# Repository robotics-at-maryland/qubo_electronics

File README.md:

# qubo_electronics

Welcome to the electronics repo for Project QUBO.
QUBO is an autonomous underwater vehicle and all of its electronics designs are stored here.

We use EAGLE for our circuit CAD.

eagleLibraries stores all the eagle libraries.

eagleDesigns sores all the boards that we design. Any design in this folder should ONLY USE COMPONENTS FROM THE eagleLibraries FOLDER.

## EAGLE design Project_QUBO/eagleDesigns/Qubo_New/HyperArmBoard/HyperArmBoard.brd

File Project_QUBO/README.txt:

This is the electronics folder for Project QUBO, the replacement for Tortuga 4.
===============================================================================

eagleLibraries is the EAGLE library folder.
	ALL robot PCB designs MUST only contain parts from libraries in the eagleLibraries directory.

datasheets is for all part datasheets used in the electronics designs.
	No subdirectories

eagleDesigns is for the actual eagle design files. 
	Subdirectories are created on a BOARD-BY-BOARD basis.
	If you're creating a new PCB, make a new folder. If you're editing an existing board, stay in the same folder.
	Use reason when creating new versions of files.

designDocumentation  is for design documentation.
	Use reason with file naming, no subdirectories.
	Document your design process ie. what your goal is, what options you considered, why you chose what you did, outline your final design selection, etc.
	Brownie points for LaTeX

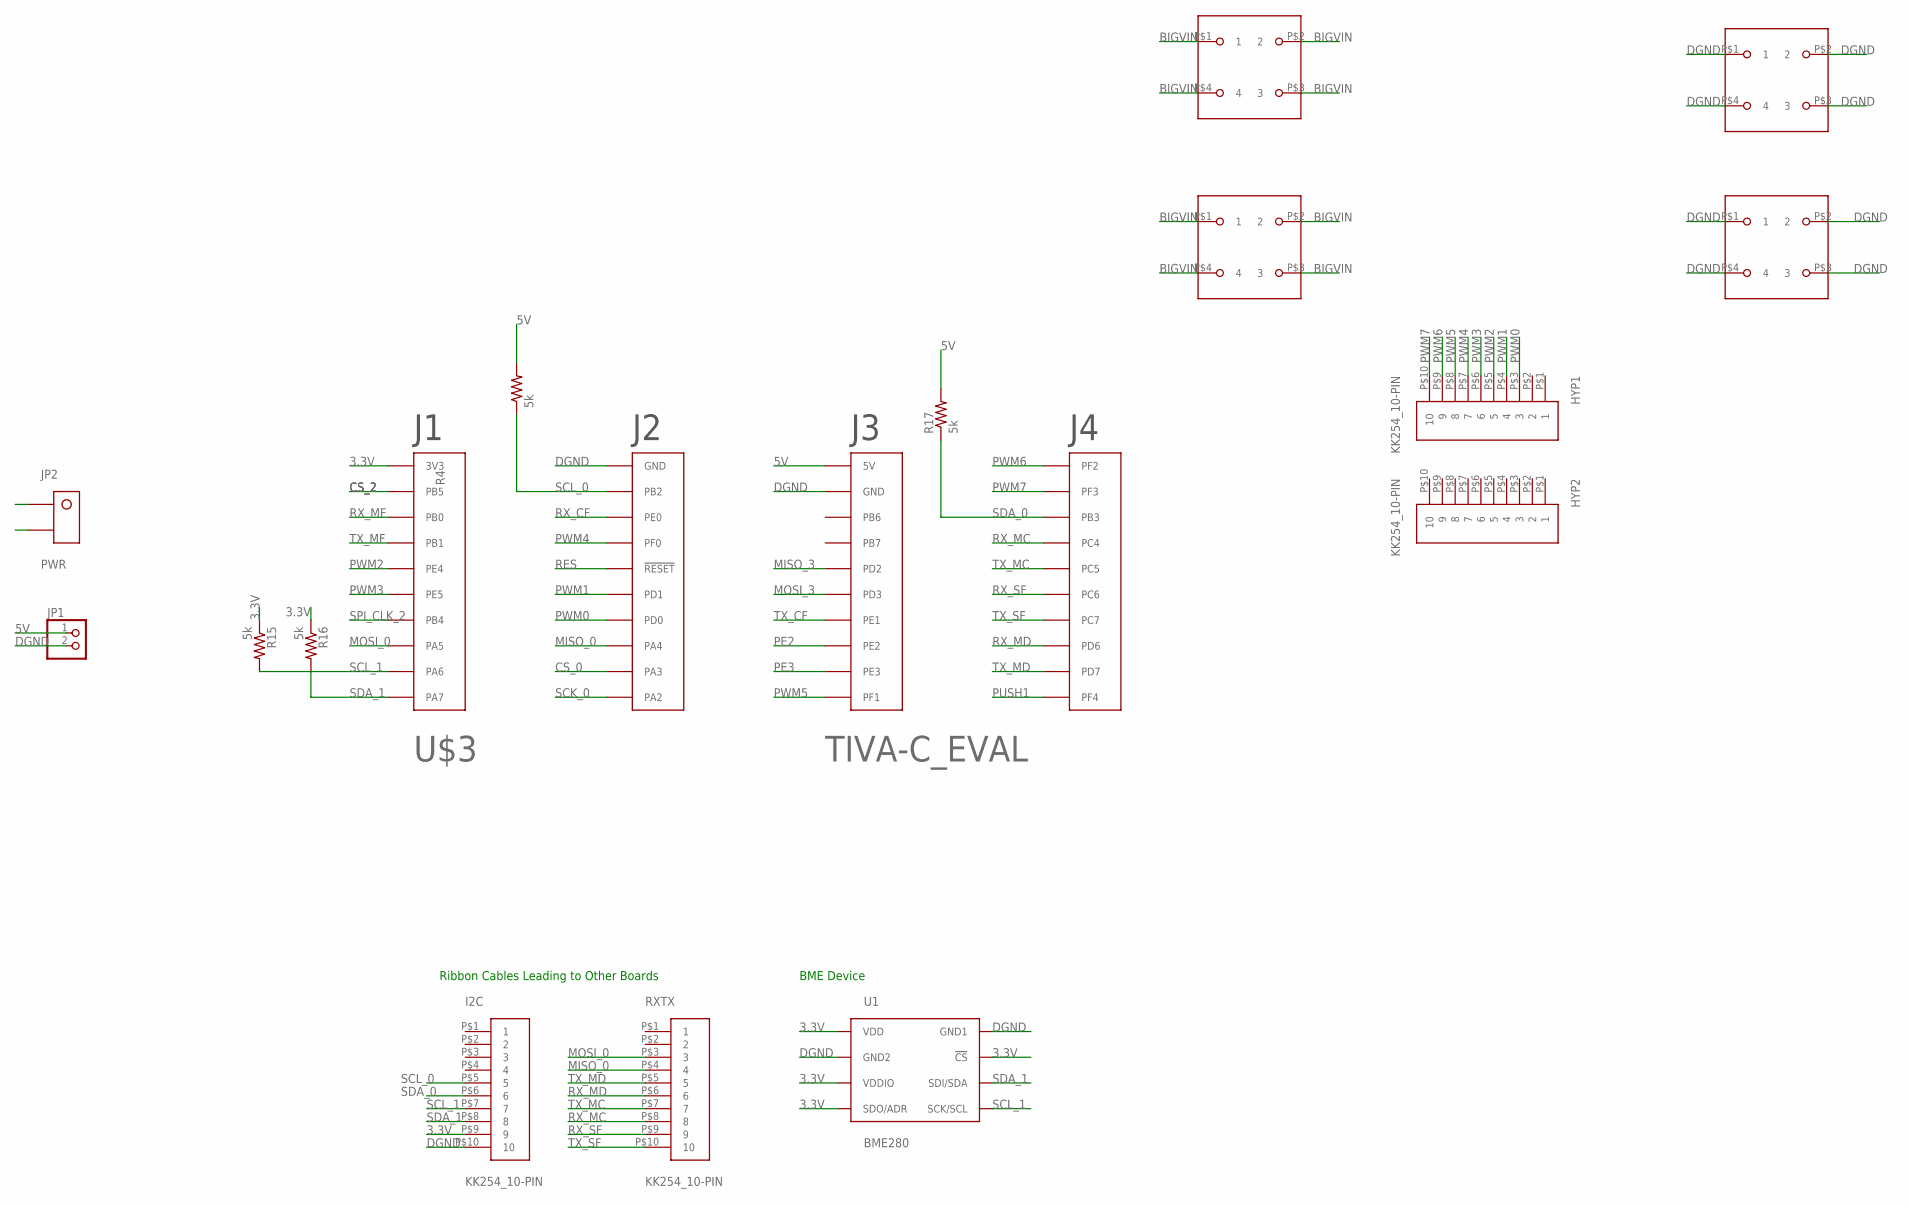
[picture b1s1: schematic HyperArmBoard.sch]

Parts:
HYP1, HYP2: KK254_10-PIN
I2C: KK254_10-PIN
JP1: PINHD-1X2; 1X02
JP2: PWR; SUPERSABRE_2CIRCUIT
R4, R15, R16, R17: 5k; R0805
RXTX: KK254_10-PIN
U1: BME280; BME280_LGA
U$3: TIVA-C_EVAL
U$4, U$5, U$6, U$7: BCS-106-L-D-PE-BE; 4-PIN-BIGPOWER

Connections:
3.3V: I2C.P$9 (9), R15.1, R16.1, U1.P$2 (!CS), U1.P$5 (SDO/ADR), U1.P$6 (VDDIO), U1.P$8 (VDD), U$3.1-1 (3V3)
5V: JP1.1, R4.2, R17.2, U$3.3-1 (5V)
BIGVIN: JP2.P$1, U$4.P$1 (1), U$4.P$2 (2), U$4.P$3 (3), U$4.P$4 (4), U$5.P$1 (1), U$5.P$2 (2), U$5.P$3 (3), U$5.P$4 (4)
CS_0: U$3.2-9 (PA3)
CS_2: U$3.1-2 (PB5)
DGND: I2C.P$10 (10), JP1.2, JP2.P$2, U1.P$1 (GND1), U1.P$7 (GND2), U$3.2-1 (GND), U$3.3-2 (GND), U$6.P$1 (1), U$6.P$2 (2), U$6.P$3 (3), U$6.P$4 (4), U$7.P$1 (1), U$7.P$2 (2), U$7.P$3 (3), U$7.P$4 (4)
MISO_0: RXTX.P$4 (4), U$3.2-8 (PA4)
MISO_3: U$3.3-5 (PD2)
MOSI_0: RXTX.P$3 (3), U$3.1-8 (PA5)
MOSI_3: U$3.3-6 (PD3)
PE2: U$3.3-8 (PE2)
PE3: U$3.3-9 (PE3)
PUSH1: U$3.4-10 (PF4)
PWM0: HYP1.P$3 (3), U$3.2-7 (PD0)
PWM1: HYP1.P$4 (4), U$3.2-6 (PD1)
PWM2: HYP1.P$5 (5), U$3.1-5 (PE4)
PWM3: HYP1.P$6 (6), U$3.1-6 (PE5)
PWM4: HYP1.P$7 (7), U$3.2-4 (PF0)
PWM5: HYP1.P$8 (8), U$3.3-10 (PF1)
PWM6: HYP1.P$9 (9), U$3.4-1 (PF2)
PWM7: HYP1.P$10 (10), U$3.4-2 (PF3)
RES: U$3.2-5 (!RESET!)
RX_CF: U$3.2-3 (PE0)
RX_MC: RXTX.P$8 (8), U$3.4-4 (PC4)
RX_MD: RXTX.P$6 (6), U$3.4-8 (PD6)
RX_MF: U$3.1-3 (PB0)
RX_SF: RXTX.P$9 (9), U$3.4-6 (PC6)
SCK_0: U$3.2-10 (PA2)
SCL_0: I2C.P$5 (5), R4.1, U$3.2-2 (PB2)
SCL_1: I2C.P$7 (7), R15.2, U1.P$4 (SCK/SCL), U$3.1-9 (PA6)
SDA_0: I2C.P$6 (6), R17.1, U$3.4-3 (PB3)
SDA_1: I2C.P$8 (8), R16.2, U1.P$3 (SDI/SDA), U$3.1-10 (PA7)
SPI_CLK_2: U$3.1-7 (PB4)
TX_CF: U$3.3-7 (PE1)
TX_MC: RXTX.P$7 (7), U$3.4-5 (PC5)
TX_MD: RXTX.P$5 (5), U$3.4-9 (PD7)
TX_MF: U$3.1-4 (PB1)
TX_SF: RXTX.P$10 (10), U$3.4-7 (PC7)

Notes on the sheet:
Ribbon Cables Leading to Other Boards
BME Device

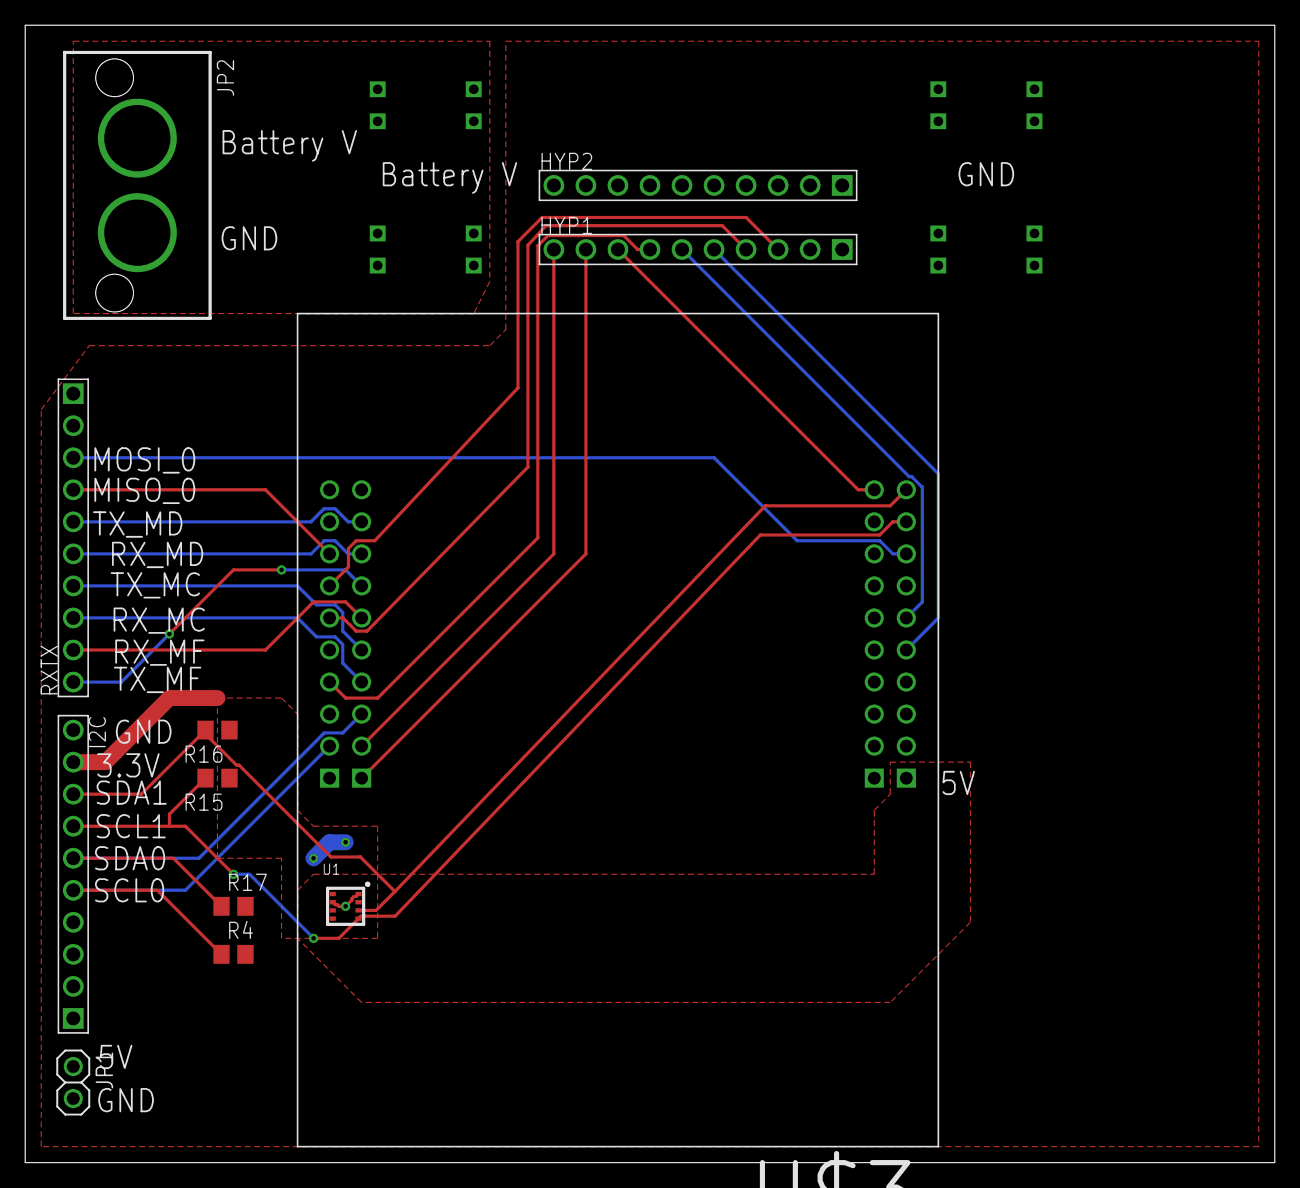
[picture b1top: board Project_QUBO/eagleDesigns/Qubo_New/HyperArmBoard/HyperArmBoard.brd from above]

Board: 2 copper layers, 99.1 x 90.2 mm, 16 parts (0 on the bottom side), 24 nets.

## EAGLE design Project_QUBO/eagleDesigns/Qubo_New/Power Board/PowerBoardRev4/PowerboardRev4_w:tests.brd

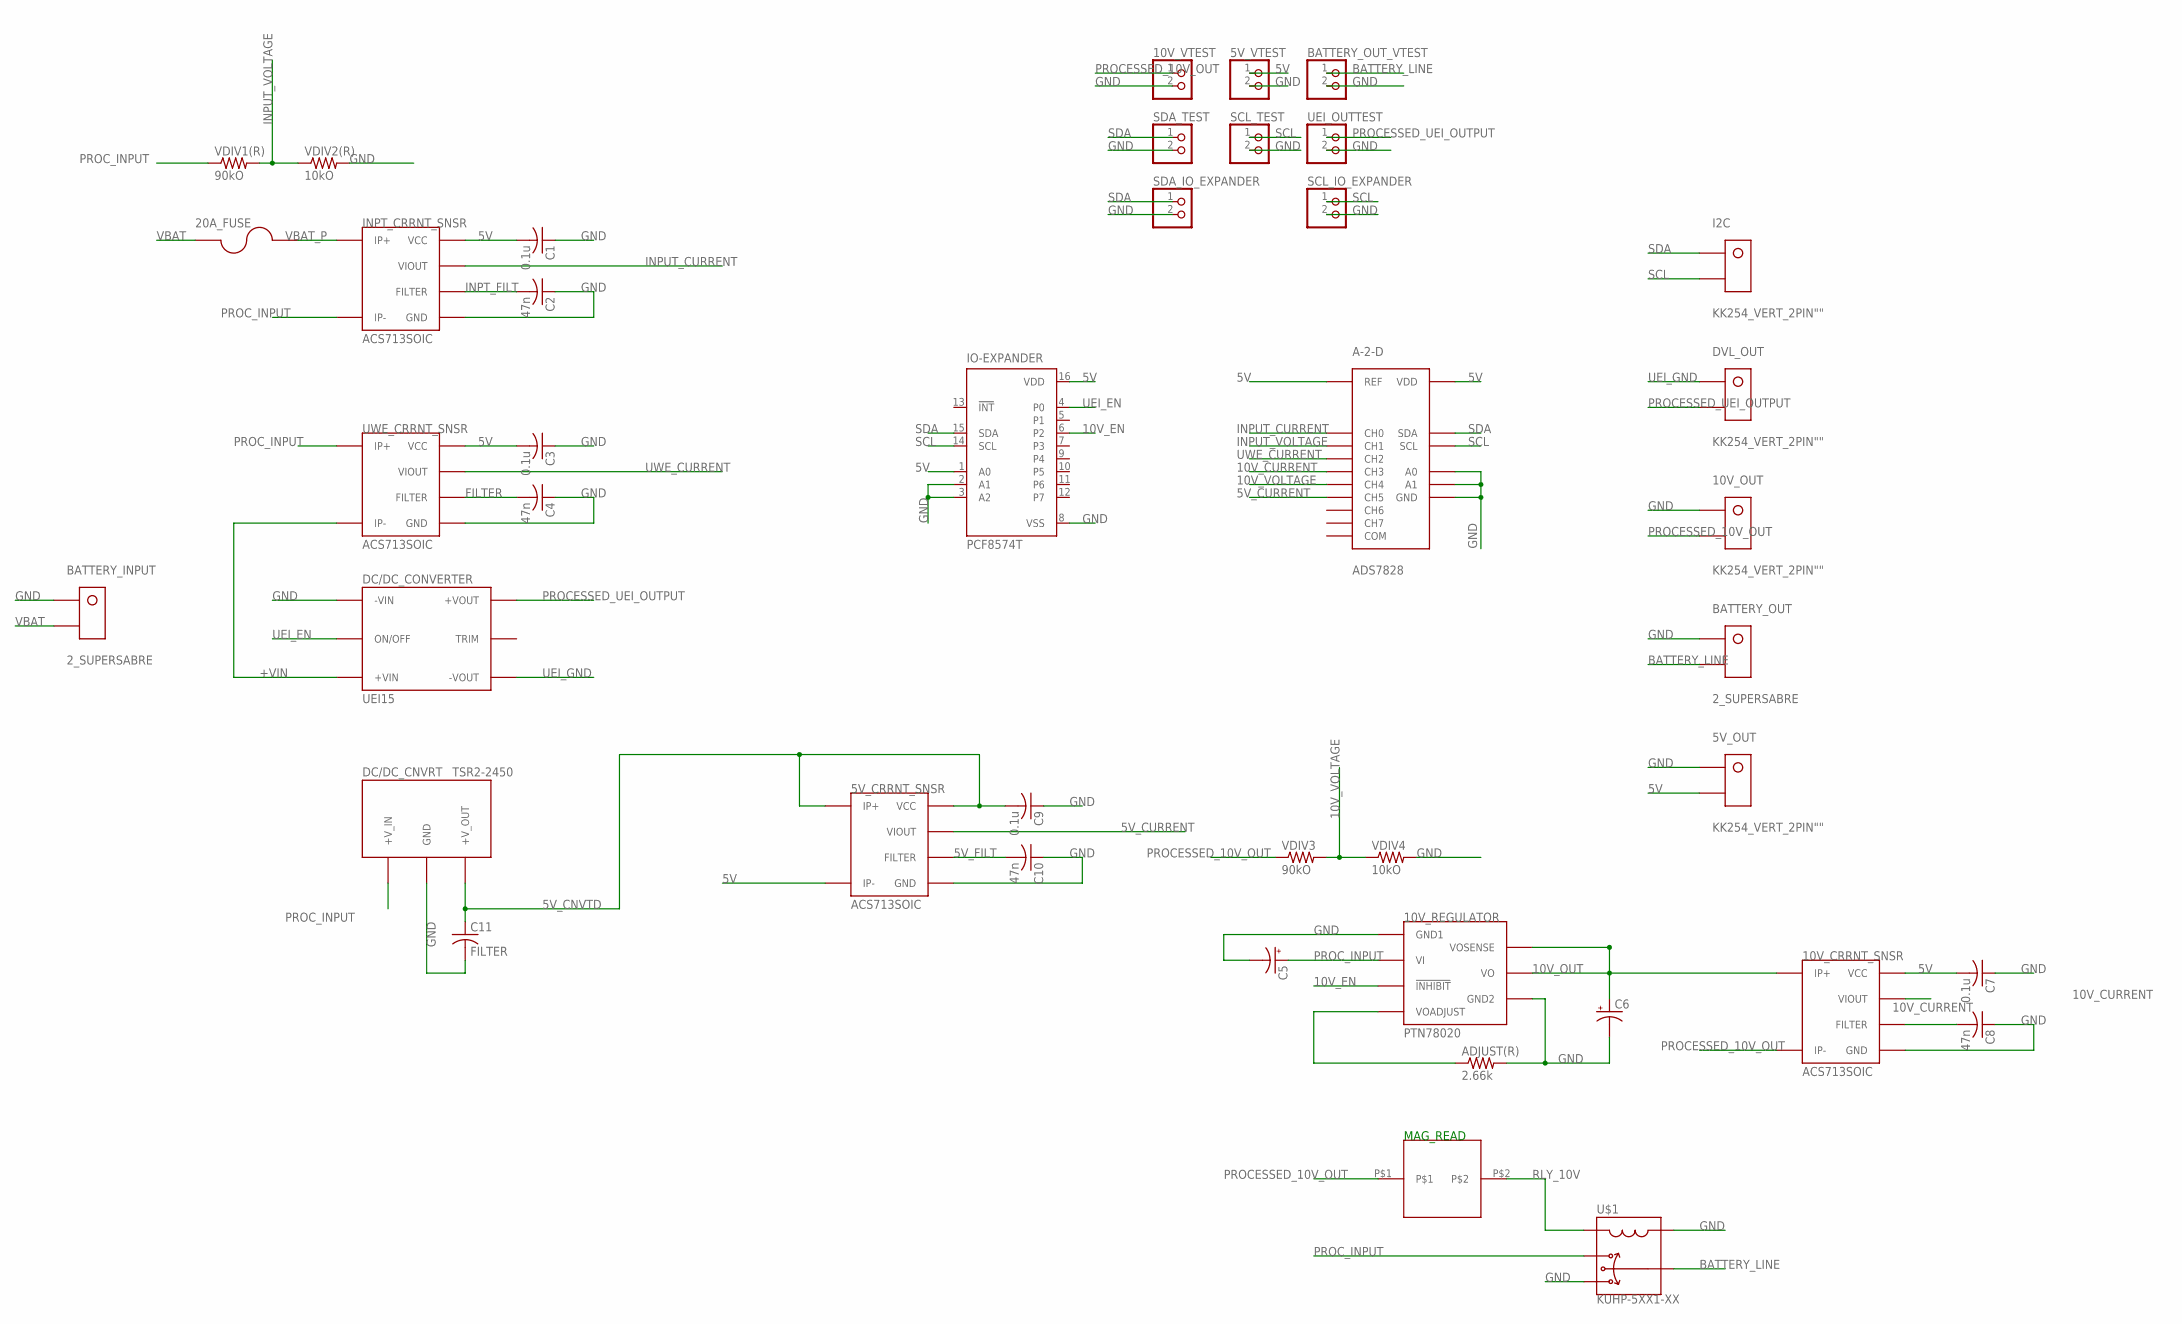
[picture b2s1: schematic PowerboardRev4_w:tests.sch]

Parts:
5V_CRRNT_SNSR, 10V_CRRNT_SNSR: ACS713SOIC; ACS713-SOIC
5V_OUT, 10V_OUT: KK254_VERT_2PIN""; KK254_VERT_2PIN
5V_VTEST, 10V_VTEST: PINHD-1X2; 1X02
10V_REGULATOR: PTN78020; PTN
20A_FUSE: BOWED-1.25"-FUSECLIPS; 1.25"_FUSECLIPS
A-2-D: ADS7828; TSSOP16
ADJUST(R): 2.66k; R0805
BATTERY_INPUT: 2_SUPERSABRE; SUPERSABRE_2CIRCUIT
BATTERY_OUT: 2_SUPERSABRE; SUPERSABRE_2CIRCUIT
BATTERY_OUT_VTEST: PINHD-1X2; 1X02
C1, C3, C7, C9: 0.1u; C0805
C2, C4, C8, C10: 47n; C0805
C5, C6: CPOL-US; PANASONIC_A_TYPE_M
C11: FILTER; C0805
DC/DC_CNVRT: TSR2-2450; TSR2
DC/DC_CONVERTER: UEI15
DVL_OUT: KK254_VERT_2PIN""; KK254_VERT_2PIN
I2C: KK254_VERT_2PIN""; KK254_VERT_2PIN
INPT_CRRNT_SNSR: ACS713SOIC; ACS713-SOIC
IO-EXPANDER: PCF8574T; SO16W
MAGREAD: HE151TR-ND
SCL_IO_EXPANDER: PINHD-1X2; 1X02
SCL_TEST: PINHD-1X2; 1X02
SDA_IO_EXPANDER: PINHD-1X2; 1X02
SDA_TEST: PINHD-1X2; 1X02
U$1: KUHP-5XX1-XX; KUHP_6.35MM-QUICK-CONNECT
UEI_OUTTEST: PINHD-1X2; 1X02
UWE_CRRNT_SNSR: ACS713SOIC; ACS713-SOIC
VDIV1(R), VDIV3: 90kO; R0805
VDIV2(R), VDIV4: 10kO; R0805

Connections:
5V: 5V_CRRNT_SNSR.P$3 (IP-), 5V_CRRNT_SNSR.P$4 (IP-), 5V_OUT.P$2, 5V_VTEST.1, 10V_CRRNT_SNSR.P$8 (VCC), A-2-D.10 (REF), A-2-D.16 (VDD), C1.2, C3.2, C7.2, INPT_CRRNT_SNSR.P$8 (VCC), IO-EXPANDER.1 (A0), IO-EXPANDER.16 (VDD), UWE_CRRNT_SNSR.P$8 (VCC)
5V_CNVTD: 5V_CRRNT_SNSR.P$1 (IP+), 5V_CRRNT_SNSR.P$2 (IP+), 5V_CRRNT_SNSR.P$8 (VCC), C9.2, C11.1, DC/DC_CNVRT.3 (+V_OUT)
5V_CURRENT: 5V_CRRNT_SNSR.P$7 (VIOUT), A-2-D.6 (CH5)
5V_FILT: 5V_CRRNT_SNSR.P$6 (FILTER), C10.2
10V_CURRENT: 10V_CRRNT_SNSR.P$7 (VIOUT), A-2-D.4 (CH3)
10V_EN: 10V_REGULATOR.INHIBIT (!INHIBIT!), IO-EXPANDER.6 (P2)
10V_OUT: 10V_CRRNT_SNSR.P$1 (IP+), 10V_CRRNT_SNSR.P$2 (IP+), 10V_REGULATOR.SENSE (VOSENSE), 10V_REGULATOR.VOUT (VO), C6.+
10V_VOLTAGE: A-2-D.5 (CH4), VDIV3.2, VDIV4.1
+VIN: DC/DC_CONVERTER.+VIN, UWE_CRRNT_SNSR.P$3 (IP-), UWE_CRRNT_SNSR.P$4 (IP-)
BATTERY_LINE: BATTERY_OUT.P$2, BATTERY_OUT_VTEST.1, U$1.7A (7), U$1.7B (7)
FILTER: C4.2, UWE_CRRNT_SNSR.P$6 (FILTER)
FLTR_10V: 10V_CRRNT_SNSR.P$6 (FILTER), C8.2
GND: 5V_CRRNT_SNSR.P$5 (GND), 5V_OUT.P$1, 5V_VTEST.2, 10V_CRRNT_SNSR.P$5 (GND), 10V_OUT.P$1, 10V_REGULATOR.GND1, 10V_REGULATOR.GND2, 10V_VTEST.2, A-2-D.9 (GND), A-2-D.12 (A0), A-2-D.13 (A1), ADJUST(R).2, BATTERY_INPUT.P$1, BATTERY_OUT.P$1, BATTERY_OUT_VTEST.2, C1.1, C2.1, C3.1, C4.1, C5.-, C6.-, C7.1, C8.1, C9.1, C10.1, C11.2, DC/DC_CNVRT.2 (GND), DC/DC_CONVERTER.-VIN, INPT_CRRNT_SNSR.P$5 (GND), IO-EXPANDER.2 (A1), IO-EXPANDER.3 (A2), IO-EXPANDER.8 (VSS), SCL_IO_EXPANDER.2, SCL_TEST.2, SDA_IO_EXPANDER.2, SDA_TEST.2, U$1.5A (5), U$1.5B (5), U$1.AA (A), U$1.AB (A), UEI_OUTTEST.2, UWE_CRRNT_SNSR.P$5 (GND), VDIV2(R).2, VDIV4.2
INPT_FILT: C2.2, INPT_CRRNT_SNSR.P$6 (FILTER)
INPUT_CURRENT: A-2-D.1 (CH0), INPT_CRRNT_SNSR.P$7 (VIOUT)
INPUT_VOLTAGE: A-2-D.2 (CH1), VDIV1(R).2, VDIV2(R).1
unnamed: 10V_REGULATOR.ADJUST (VOADJUST), ADJUST(R).1
PROCESSED_10V_OUT: 10V_CRRNT_SNSR.P$3 (IP-), 10V_CRRNT_SNSR.P$4 (IP-), 10V_OUT.P$2, 10V_VTEST.1, MAGREAD.P$1, VDIV3.1
PROCESSED_UEI_OUTPUT: DC/DC_CONVERTER.+VOUT, DVL_OUT.P$2, UEI_OUTTEST.1
PROC_INPUT: 10V_REGULATOR.VIN (VI), C5.+, DC/DC_CNVRT.1 (+V_IN), INPT_CRRNT_SNSR.P$3 (IP-), INPT_CRRNT_SNSR.P$4 (IP-), U$1.2A (2), U$1.2B (2), UWE_CRRNT_SNSR.P$1 (IP+), UWE_CRRNT_SNSR.P$2 (IP+), VDIV1(R).1
RLY_10V: MAGREAD.P$2, U$1.BA (B), U$1.BB (B)
SCL: A-2-D.14 (SCL), I2C.P$2, IO-EXPANDER.14 (SCL), SCL_IO_EXPANDER.1, SCL_TEST.1
SDA: A-2-D.15 (SDA), I2C.P$1, IO-EXPANDER.15 (SDA), SDA_IO_EXPANDER.1, SDA_TEST.1
UEI_EN: DC/DC_CONVERTER.ON/OFFCNTRL (ON/OFF), IO-EXPANDER.4 (P0)
UEI_GND: DC/DC_CONVERTER.-VOUT, DVL_OUT.P$1
UWE_CURRENT: A-2-D.3 (CH2), UWE_CRRNT_SNSR.P$7 (VIOUT)
VBAT: 20A_FUSE.P$1, 20A_FUSE.P$2, BATTERY_INPUT.P$2
VBAT_P: 20A_FUSE.P$3, 20A_FUSE.P$4, INPT_CRRNT_SNSR.P$1 (IP+), INPT_CRRNT_SNSR.P$2 (IP+)

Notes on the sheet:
MAG_READ

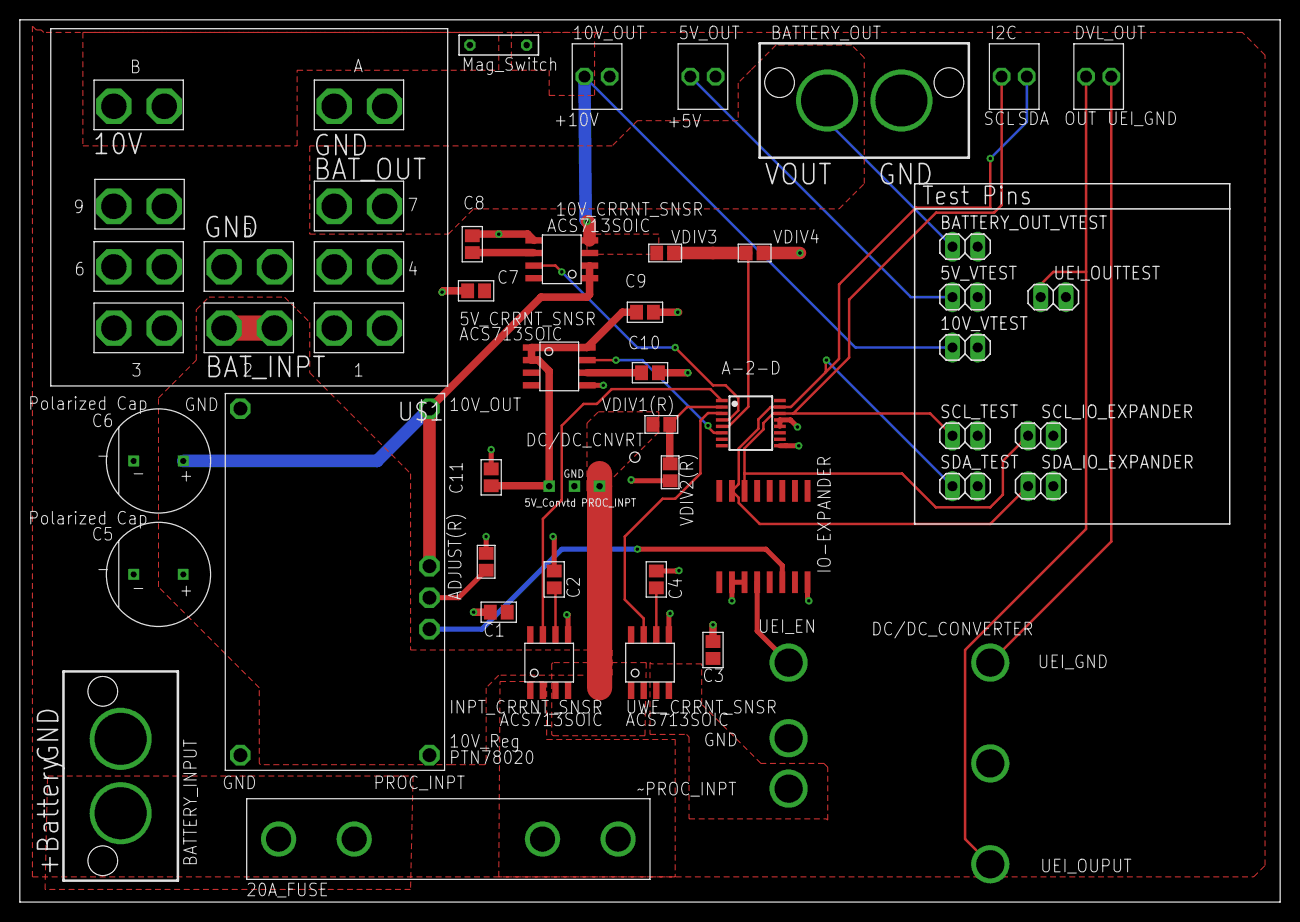
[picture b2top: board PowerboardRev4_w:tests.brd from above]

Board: 2 copper layers, 127.0 x 88.9 mm, 42 parts (0 on the bottom side), 28 nets.

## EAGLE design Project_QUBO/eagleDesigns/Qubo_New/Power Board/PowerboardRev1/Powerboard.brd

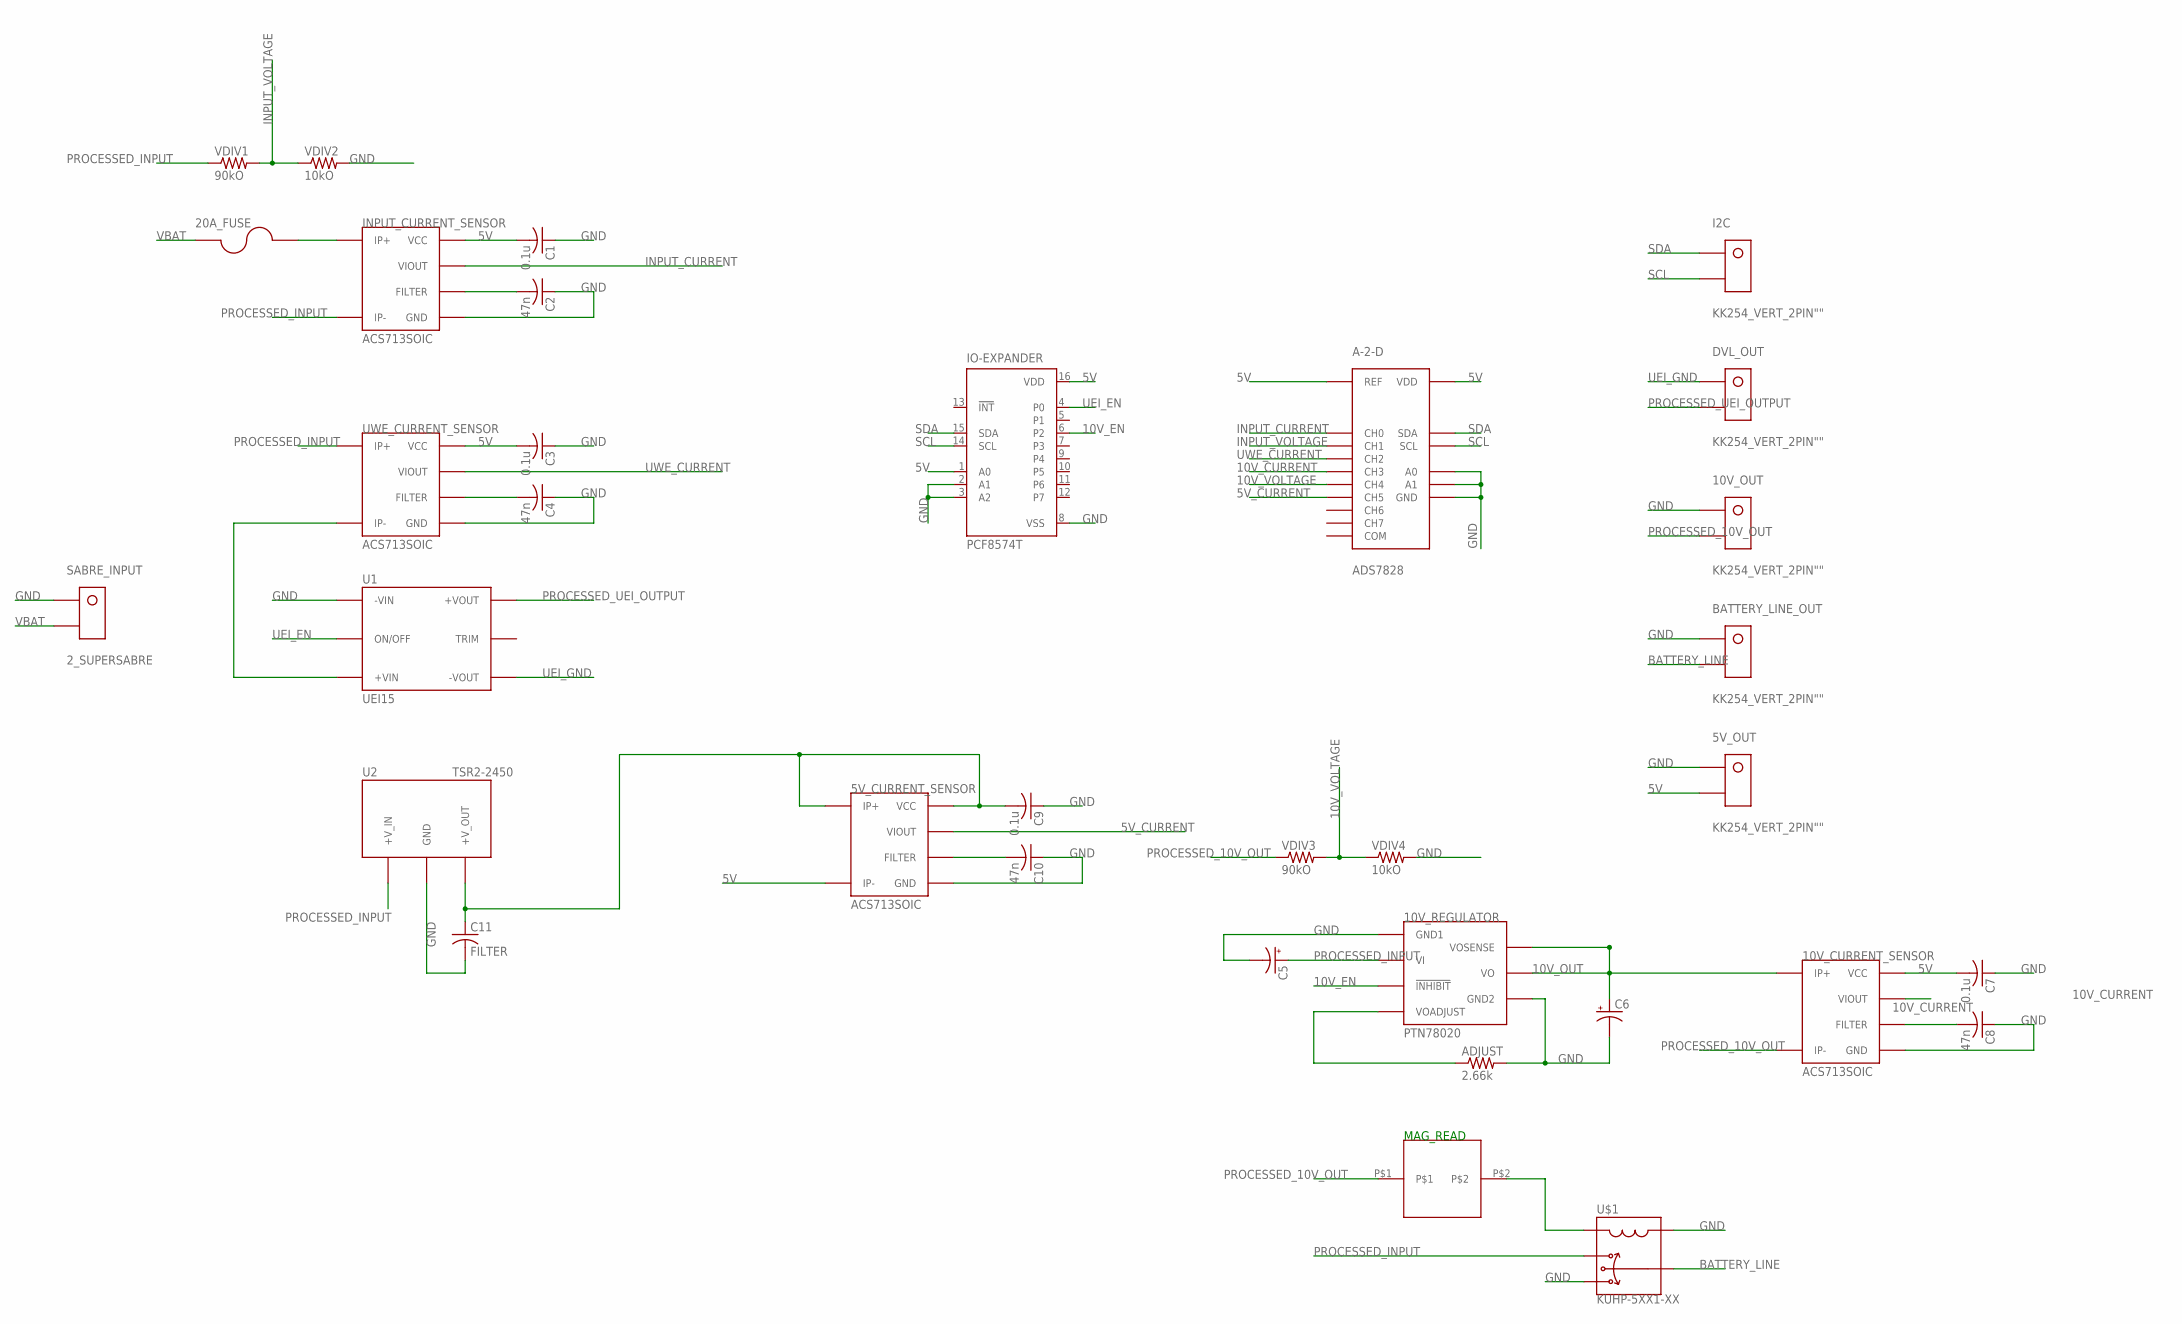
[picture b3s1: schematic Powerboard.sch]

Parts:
5V_CURRENT_SENSOR, 10V_CURRENT_SENSOR: ACS713SOIC; ACS713-SOIC
5V_OUT, 10V_OUT: KK254_VERT_2PIN""; KK254_VERT_2PIN
10V_REGULATOR: PTN78020; PTN
20A_FUSE: BOWED-1.25"-FUSECLIPS; 1.25"_FUSECLIPS
A-2-D: ADS7828; TSSOP16
ADJUST: 2.66k; R0805
BATTERY_LINE_OUT: KK254_VERT_2PIN""; KK254_VERT_2PIN
C1, C3, C7, C9: 0.1u; C0805
C2, C4, C8, C10: 47n; C0805
C5, C6: CPOL-US; PANASONIC_A_TYPE_M
C11: FILTER; C0805
DVL_OUT: KK254_VERT_2PIN""; KK254_VERT_2PIN
I2C: KK254_VERT_2PIN""; KK254_VERT_2PIN
INPUT_CURRENT_SENSOR: ACS713SOIC; ACS713-SOIC
IO-EXPANDER: PCF8574T; SO16W
MAGREAD: HE151TR-ND
SABRE_INPUT: 2_SUPERSABRE; SUPERSABRE_2CIRCUIT
U1: UEI15
U2: TSR2-2450; TSR2
U$1: KUHP-5XX1-XX; KUHP_6.35MM-QUICK-CONNECT
UWE_CURRENT_SENSOR: ACS713SOIC; ACS713-SOIC
VDIV1, VDIV3: 90kO; R0805
VDIV2, VDIV4: 10kO; R0805

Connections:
5V: 5V_CURRENT_SENSOR.P$3 (IP-), 5V_CURRENT_SENSOR.P$4 (IP-), 5V_OUT.P$2, 10V_CURRENT_SENSOR.P$8 (VCC), A-2-D.10 (REF), A-2-D.16 (VDD), C1.2, C3.2, C7.2, INPUT_CURRENT_SENSOR.P$8 (VCC), IO-EXPANDER.1 (A0), IO-EXPANDER.16 (VDD), UWE_CURRENT_SENSOR.P$8 (VCC)
5V_CURRENT: 5V_CURRENT_SENSOR.P$7 (VIOUT), A-2-D.6 (CH5)
10V_CURRENT: 10V_CURRENT_SENSOR.P$7 (VIOUT), A-2-D.4 (CH3)
10V_EN: 10V_REGULATOR.INHIBIT (!INHIBIT!), IO-EXPANDER.6 (P2)
10V_OUT: 10V_CURRENT_SENSOR.P$1 (IP+), 10V_CURRENT_SENSOR.P$2 (IP+), 10V_REGULATOR.SENSE (VOSENSE), 10V_REGULATOR.VOUT (VO), C6.+
10V_VOLTAGE: A-2-D.5 (CH4), VDIV3.2, VDIV4.1
BATTERY_LINE: BATTERY_LINE_OUT.P$2, U$1.7A (7), U$1.7B (7)
GND: 5V_CURRENT_SENSOR.P$5 (GND), 5V_OUT.P$1, 10V_CURRENT_SENSOR.P$5 (GND), 10V_OUT.P$1, 10V_REGULATOR.GND1, 10V_REGULATOR.GND2, A-2-D.9 (GND), A-2-D.12 (A0), A-2-D.13 (A1), ADJUST.2, BATTERY_LINE_OUT.P$1, C1.1, C2.1, C3.1, C4.1, C5.-, C6.-, C7.1, C8.1, C9.1, C10.1, C11.2, INPUT_CURRENT_SENSOR.P$5 (GND), IO-EXPANDER.2 (A1), IO-EXPANDER.3 (A2), IO-EXPANDER.8 (VSS), SABRE_INPUT.P$1, U1.-VIN, U2.2 (GND), U$1.5A (5), U$1.5B (5), U$1.AA (A), U$1.AB (A), UWE_CURRENT_SENSOR.P$5 (GND), VDIV2.2, VDIV4.2
INPUT_CURRENT: A-2-D.1 (CH0), INPUT_CURRENT_SENSOR.P$7 (VIOUT)
INPUT_VOLTAGE: A-2-D.2 (CH1), VDIV1.2, VDIV2.1
unnamed: 20A_FUSE.P$3, 20A_FUSE.P$4, INPUT_CURRENT_SENSOR.P$1 (IP+), INPUT_CURRENT_SENSOR.P$2 (IP+)
unnamed: C2.2, INPUT_CURRENT_SENSOR.P$6 (FILTER)
unnamed: 5V_CURRENT_SENSOR.P$6 (FILTER), C10.2
unnamed: 5V_CURRENT_SENSOR.P$1 (IP+), 5V_CURRENT_SENSOR.P$2 (IP+), 5V_CURRENT_SENSOR.P$8 (VCC), C9.2, C11.1, U2.3 (+V_OUT)
unnamed: 10V_REGULATOR.ADJUST (VOADJUST), ADJUST.1
unnamed: U1.+VIN, UWE_CURRENT_SENSOR.P$3 (IP-), UWE_CURRENT_SENSOR.P$4 (IP-)
unnamed: C4.2, UWE_CURRENT_SENSOR.P$6 (FILTER)
unnamed: MAGREAD.P$2, U$1.BA (B), U$1.BB (B)
unnamed: 10V_CURRENT_SENSOR.P$6 (FILTER), C8.2
PROCESSED_10V_OUT: 10V_CURRENT_SENSOR.P$3 (IP-), 10V_CURRENT_SENSOR.P$4 (IP-), 10V_OUT.P$2, MAGREAD.P$1, VDIV3.1
PROCESSED_INPUT: 10V_REGULATOR.VIN (VI), C5.+, INPUT_CURRENT_SENSOR.P$3 (IP-), INPUT_CURRENT_SENSOR.P$4 (IP-), U2.1 (+V_IN), U$1.2A (2), U$1.2B (2), UWE_CURRENT_SENSOR.P$1 (IP+), UWE_CURRENT_SENSOR.P$2 (IP+), VDIV1.1
PROCESSED_UEI_OUTPUT: DVL_OUT.P$2, U1.+VOUT
SCL: A-2-D.14 (SCL), I2C.P$2, IO-EXPANDER.14 (SCL)
SDA: A-2-D.15 (SDA), I2C.P$1, IO-EXPANDER.15 (SDA)
UEI_EN: IO-EXPANDER.4 (P0), U1.ON/OFFCNTRL (ON/OFF)
UEI_GND: DVL_OUT.P$1, U1.-VOUT
UWE_CURRENT: A-2-D.3 (CH2), UWE_CURRENT_SENSOR.P$7 (VIOUT)
VBAT: 20A_FUSE.P$1, 20A_FUSE.P$2, SABRE_INPUT.P$2

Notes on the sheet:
MAG_READ

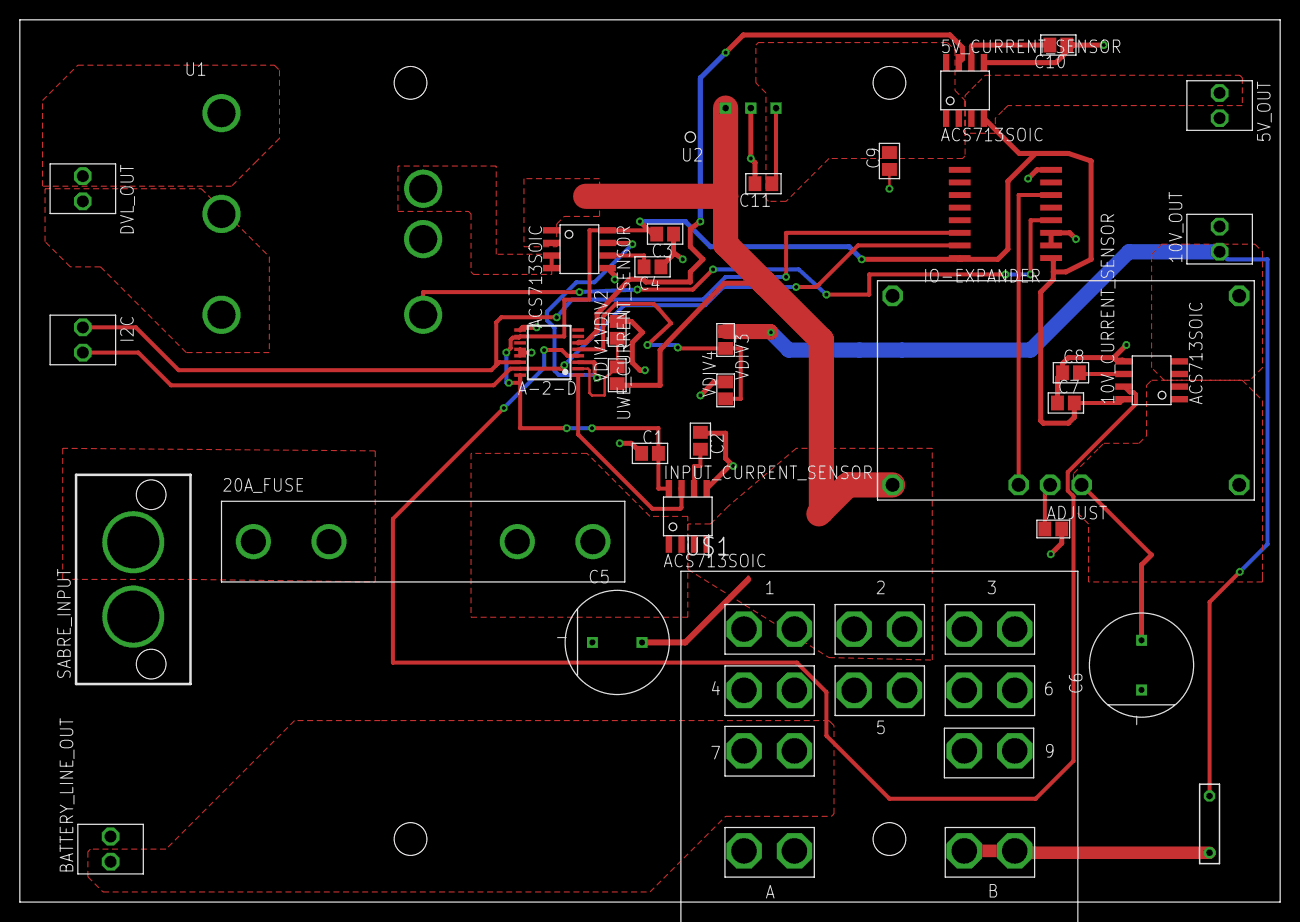
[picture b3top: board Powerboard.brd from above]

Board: 2 copper layers, 127.0 x 88.9 mm, 34 parts (0 on the bottom side), 28 nets.

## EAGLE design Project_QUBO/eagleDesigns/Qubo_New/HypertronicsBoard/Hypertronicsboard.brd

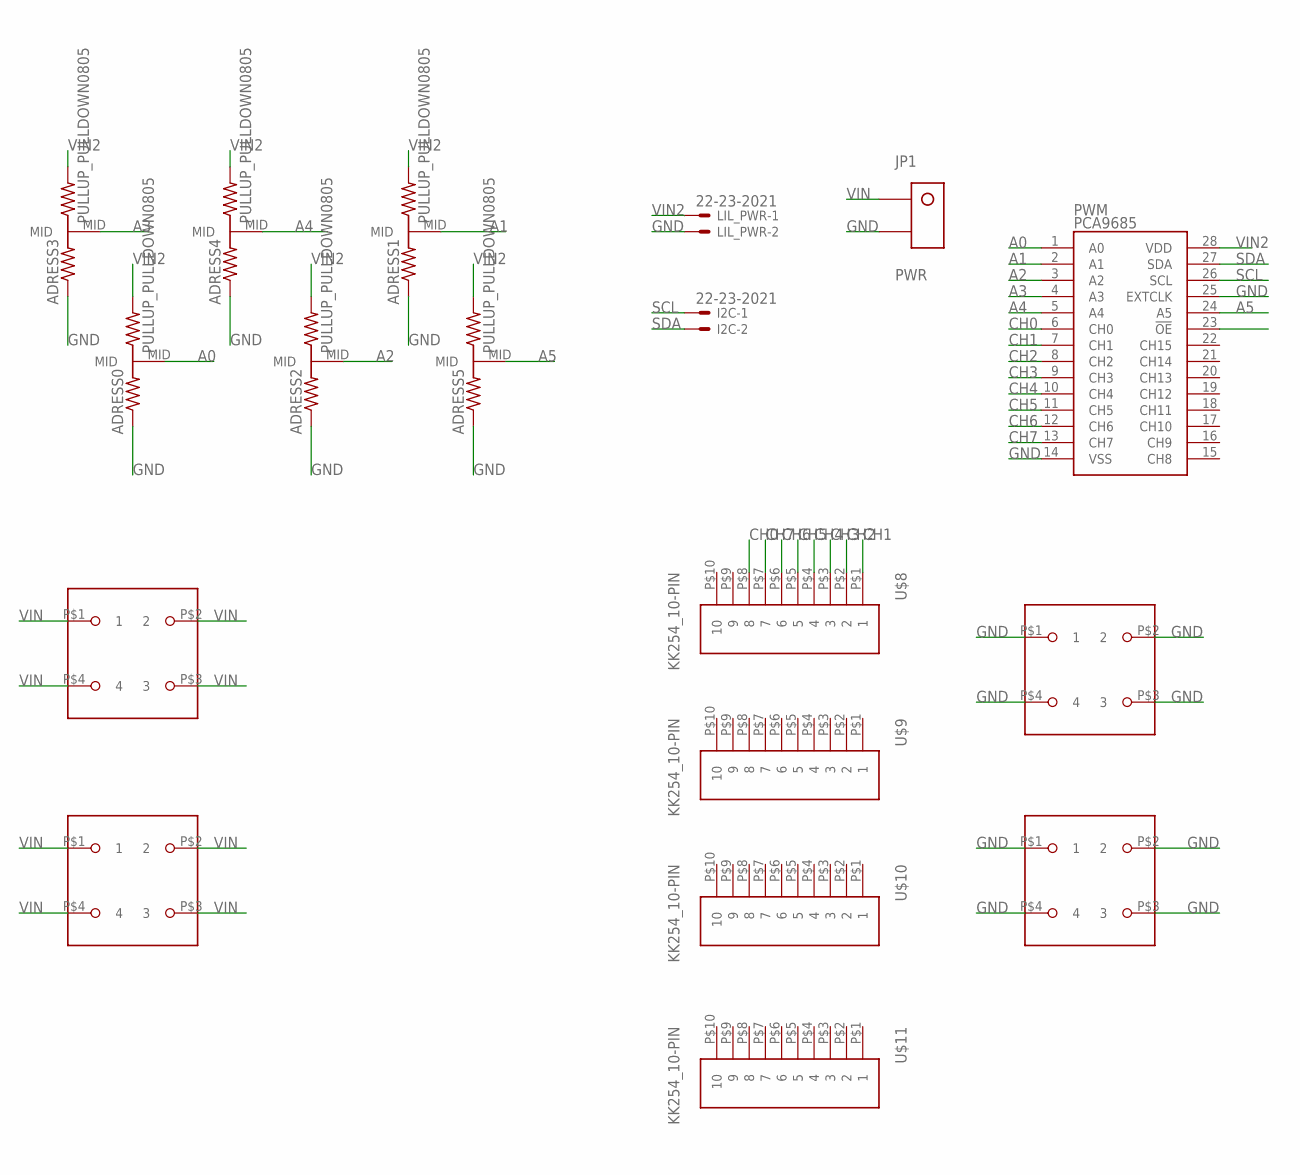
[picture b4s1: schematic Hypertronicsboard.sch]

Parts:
ADRESS0, ADRESS1, ADRESS2, ADRESS3, ADRESS4, ADRESS5: PULLUP_PULLDOWN0805; PULLUP_PULLDOWN_0805
I2C: 22-23-2021
JP1: PWR; SUPERSABRE_2CIRCUIT
LIL_PWR: 22-23-2021
PWM: PCA9685; TSSOP-28_4MM
U$1, U$2, U$3, U$4: BCS-106-L-D-PE-BE; 4-PIN-BIGPOWER
U$8, U$9, U$10, U$11: KK254_10-PIN

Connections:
A0: ADRESS0.MID, PWM.1 (A0)
A1: ADRESS1.MID, PWM.2 (A1)
A2: ADRESS2.MID, PWM.3 (A2)
A3: ADRESS3.MID, PWM.4 (A3)
A4: ADRESS4.MID, PWM.5 (A4)
A5: ADRESS5.MID, PWM.24 (A5)
CH0: PWM.6 (CH0), U$8.P$8 (8)
CH1: PWM.7 (CH1), U$8.P$1 (1)
CH2: PWM.8 (CH2), U$8.P$2 (2)
CH3: PWM.9 (CH3), U$8.P$3 (3)
CH4: PWM.10 (CH4), U$8.P$4 (4)
CH5: PWM.11 (CH5), U$8.P$5 (5)
CH6: PWM.12 (CH6), U$8.P$6 (6)
CH7: PWM.13 (CH7), U$8.P$7 (7)
GND: ADRESS0.GND, ADRESS1.GND, ADRESS2.GND, ADRESS3.GND, ADRESS4.GND, ADRESS5.GND, JP1.P$2, LIL_PWR.2, PWM.14 (VSS), PWM.25 (EXTCLK), U$3.P$1 (1), U$3.P$2 (2), U$3.P$3 (3), U$3.P$4 (4), U$4.P$1 (1), U$4.P$2 (2), U$4.P$3 (3), U$4.P$4 (4)
SCL: I2C.1, PWM.26 (SCL)
SDA: I2C.2, PWM.27 (SDA)
VIN: JP1.P$1, U$1.P$1 (1), U$1.P$2 (2), U$1.P$3 (3), U$1.P$4 (4), U$2.P$1 (1), U$2.P$2 (2), U$2.P$3 (3), U$2.P$4 (4)
VIN2: ADRESS0.VCC (PWR), ADRESS1.VCC (PWR), ADRESS2.VCC (PWR), ADRESS3.VCC (PWR), ADRESS4.VCC (PWR), ADRESS5.VCC (PWR), LIL_PWR.1, PWM.28 (VDD)

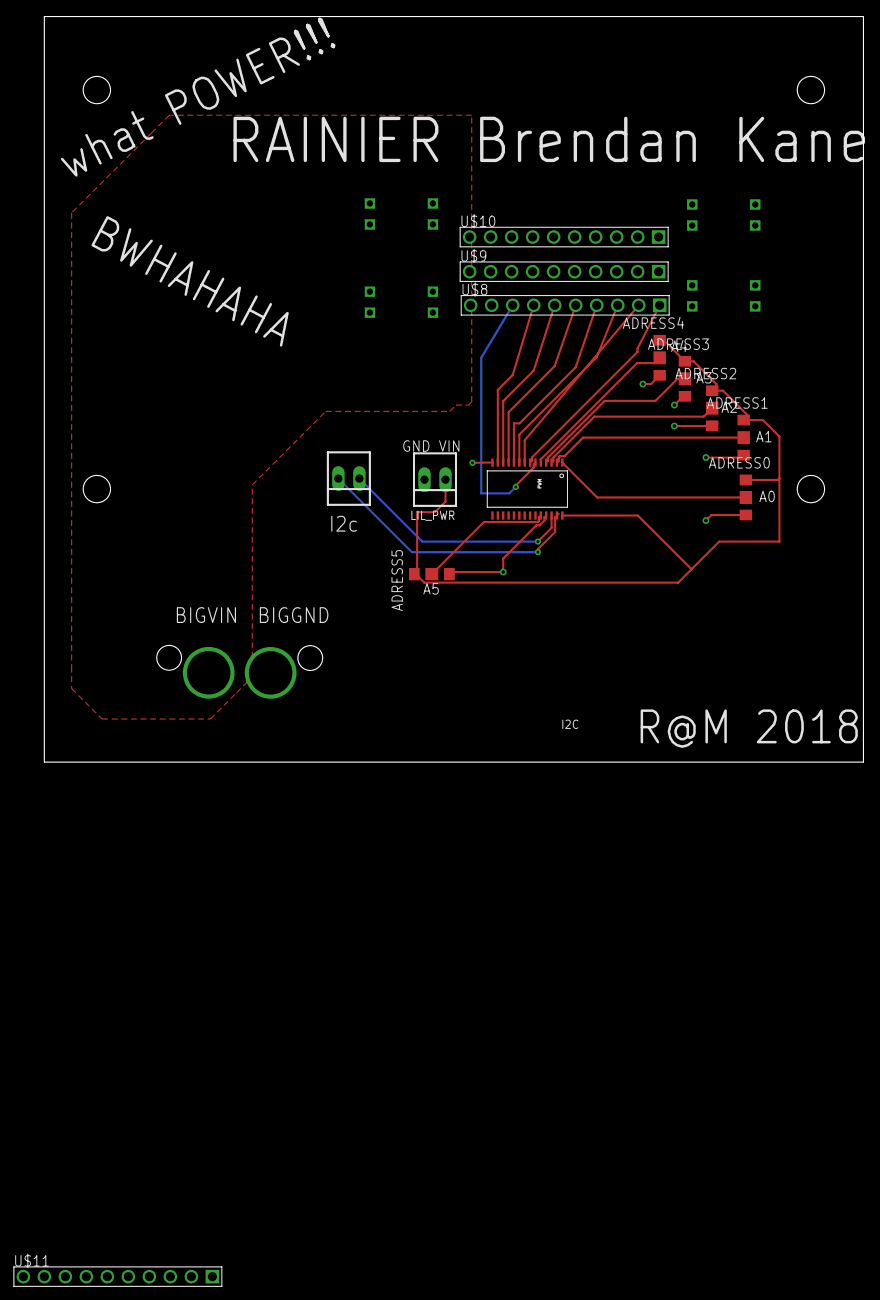
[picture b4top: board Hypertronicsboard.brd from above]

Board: 2 copper layers, 99.1 x 90.2 mm, 18 parts (1 on the bottom side), 19 nets.

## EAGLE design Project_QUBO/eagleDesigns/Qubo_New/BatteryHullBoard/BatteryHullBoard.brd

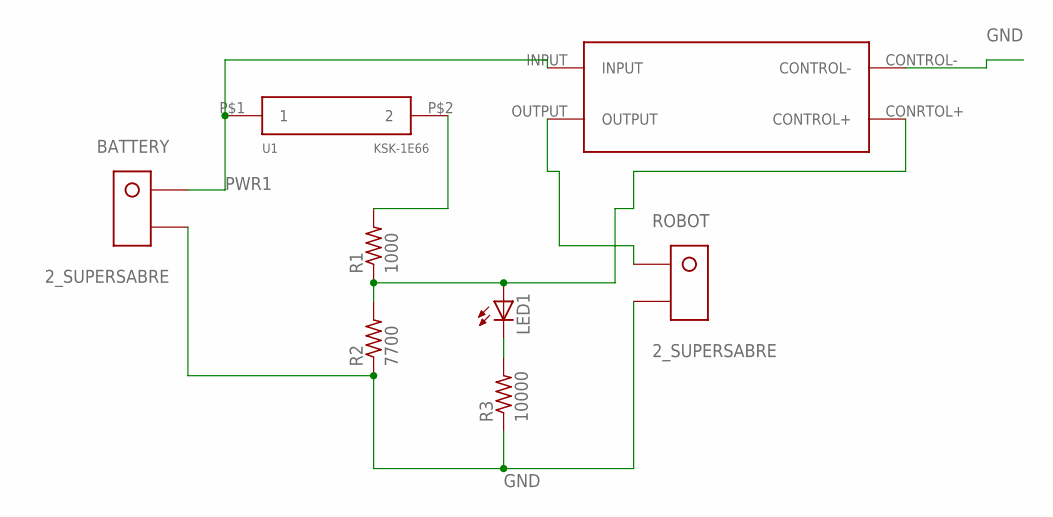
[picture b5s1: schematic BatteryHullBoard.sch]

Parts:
BATTERY: 2_SUPERSABRE; SUPERSABRE_2CIRCUIT
LED1: LED5MM
R1: 1000; R0805
R2: 7700; R0805
R3: 10000; R0805
ROBOT: 2_SUPERSABRE; SUPERSABRE_2CIRCUIT
U1: KSK-1E66
U$1: ADJH21112

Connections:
GND: BATTERY.P$2, R2.1, R3.1, ROBOT.P$2, U$1.CONTROL-
unnamed: R1.2, U1.P$2 (2)
unnamed: LED1.A, R1.1, R2.2, U$1.CONRTOL+ (CONTROL+)
unnamed: LED1.K (C), R3.2
PWR1: BATTERY.P$1, U1.P$1 (1), U$1.INPUT
PWR2: ROBOT.P$1, U$1.OUTPUT
